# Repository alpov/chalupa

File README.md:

# chalupa
Cottage GSM Weather Station

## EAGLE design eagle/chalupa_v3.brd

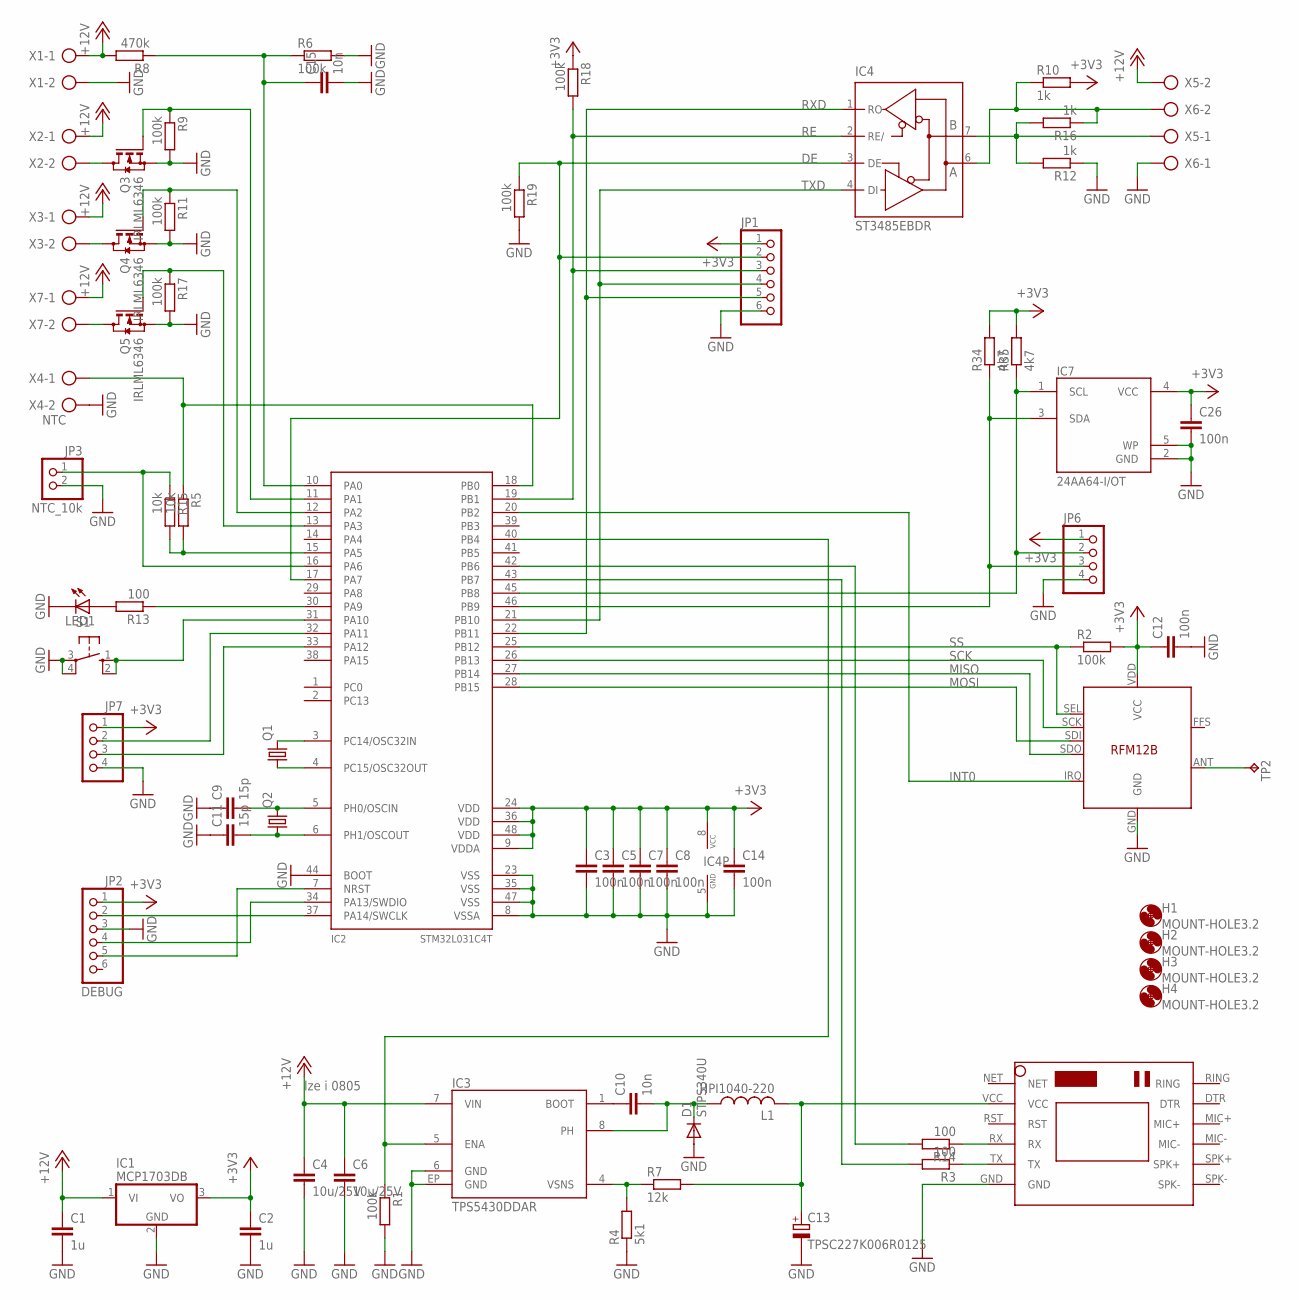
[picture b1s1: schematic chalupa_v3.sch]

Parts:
C1, C2: 1u; C0603
C3, C5, C7, C8, C12, C14, C26: 100n; C0603
C4, C6: 10u/25V; C1206
C9, C11: 15p; C0603
C10, C15: 10n; C0603
C13: TPSC227K006R0125; SMC_C
D1: STPS340U; SMB
H1, H2, H3, H4: MOUNT-HOLE3.2; 3,2
IC1: MCP1703DB; SOT223
IC2: STM32L031C4T; LQFP48
IC3: TPS5430DDAR; DDA
IC4: ST3485EBDR; SO08
IC5: SIM800LMODULE
IC7: 24AA64-I/OT; SOT23-5
JP1: PINHD-1X6; 1X06
JP2: DEBUG; 1X06
JP3: NTC_10k; 1X02
JP6, JP7: PINHD-1X4; 1X04
L1: HPI1040-220; HPI1040
LED1: LEDCHIP-LED0805; CHIP-LED0805
Q1: CRYSTALTC38H; TC38H
Q2: CRYSTALHC49UP; HC49UP
Q3, Q4, Q5: IRLML6346; SOT23
R1, R2, R6, R9, R11, R17, R18, R19: 100k; R0603
R3, R13, R14: 100; R0603
R4: 5k1; R0603
R5, R15: 10k; R0603
R7: 12k; R0603
R8: 470k; R0603
R10, R12, R16: 1k; R0603
R34, R35: 4k7; R0603
RFM12B: RFM12B
S1: 10-XX; B3F-10XX
TP2: ANT868; B2,54
X1, X2, X3, X5, X6, X7: AK500/2
X4: NTC; AK500/2

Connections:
+3V3: C2.1, C3.1, C5.1, C7.1, C8.1, C12.1, C14.1, C26.1, IC1.3 (VO), IC2.9 (VDDA), IC2.24 (VDD), IC2.36 (VDD), IC2.48 (VDD), IC4.8 (VCC), IC7.4 (VCC), JP1.1, JP2.1, JP6.1, JP7.1, R2.2, R10.2, R18.1, R34.2, R35.2, RFM12B.VDD (VCC)
+12V: C1.1, C4.1, C6.1, IC1.1 (VI), IC3.7 (VIN), R8.2, X1.1, X2.1, X3.1, X5.2, X7.1
DE: IC2.17 (PA7), IC4.3 (DE), JP1.2, R19.1
EEP_SCL: IC2.45 (PB8), IC7.1 (SCL), JP6.2, R35.1
EEP_SDA: IC2.46 (PB9), IC7.3 (SDA), JP6.3, R34.1
GND: C1.2, C2.2, C3.2, C4.2, C5.2, C6.2, C7.2, C8.2, C9.1, C11.1, C12.2, C13.-, C14.2, C15.2, C26.2, D1.A, IC1.2 (GND), IC2.8 (VSSA), IC2.23 (VSS), IC2.35 (VSS), IC2.44 (BOOT), IC2.47 (VSS), IC3.6 (GND), IC3.EP (GND), IC4.5 (GND), IC5.GND, IC7.2 (GND), IC7.5 (WP), JP1.6, JP2.3, JP3.2, JP6.4, JP7.4, LED1.C, Q3.2 (S), Q4.2 (S), Q5.2 (S), R1.2, R4.1, R6.2, R9.2, R11.2, R12.1, R17.2, R19.2, RFM12B.GND, S1.3, S1.4 (P1), X1.2, X4.2, X6.1
GSM_EN: IC2.40 (PB4), IC3.5 (ENA), R1.1
INT0: IC2.20 (PB2), RFM12B.IRQ
MISO: IC2.27 (PB14), RFM12B.SDO
MOSI: IC2.28 (PB15), RFM12B.SDI
unnamed: C11.2, IC2.6 (PH1/OSCOUT), Q2.1
unnamed: IC5.TX, R3.1
unnamed: C9.2, IC2.5 (PH0/OSCIN), Q2.2
unnamed: IC2.4 (PC15/OSC32OUT), Q1.1
unnamed: IC2.3 (PC14/OSC32IN), Q1.2
unnamed: RFM12B.ANT, TP2.PP
unnamed: IC2.42 (PB6), R14.2
unnamed: C10.1, IC3.1 (BOOT)
unnamed: C13.+, IC5.VCC, L1.2, R7.2
unnamed: C10.2, D1.C, IC3.8 (PH), L1.1
unnamed: Q5.3 (D), X7.2
unnamed: IC5.RX, R14.1
unnamed: LED1.A, R13.2
unnamed: IC2.31 (PA10), S1.1 (S), S1.2 (S1)
unnamed: IC2.18 (PB0), R5.1, X4.1
unnamed: Q3.3 (D), X2.2
unnamed: Q4.3 (D), X3.2
unnamed: IC2.13 (PA3), Q5.1 (G), R17.1
unnamed: C15.1, IC2.10 (PA0), R6.1, R8.1
unnamed: IC4.7 (B), R12.2, R16.2, X5.1
unnamed: IC2.11 (PA1), Q3.1 (G), R9.1
unnamed: IC3.4 (VSNS), R4.2, R7.1
unnamed: IC2.12 (PA2), Q4.1 (G), R11.1
unnamed: IC2.15 (PA5), R5.2, R15.2
unnamed: IC2.16 (PA6), JP3.1, R15.1
unnamed: IC2.30 (PA9), R13.1
unnamed: IC2.32 (PA11), JP7.2
unnamed: IC2.33 (PA12), JP7.3
unnamed: IC4.6 (A), R10.1, R16.1, X6.2
unnamed: IC2.34 (PA13/SWDIO), JP2.4
unnamed: IC2.37 (PA14/SWCLK), JP2.2
unnamed: IC2.7 (NRST), JP2.5
RE: IC2.19 (PB1), IC4.2 (RE/), JP1.3, R18.2
RXD: IC2.22 (PB11), IC4.1 (RO), JP1.5
SCK: IC2.26 (PB13), RFM12B.SCK
SS: IC2.25 (PB12), R2.1, RFM12B.SEL
TX1: IC2.43 (PB7), R3.2
TXD: IC2.21 (PB10), IC4.4 (DI), JP1.4

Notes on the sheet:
lze i 0805

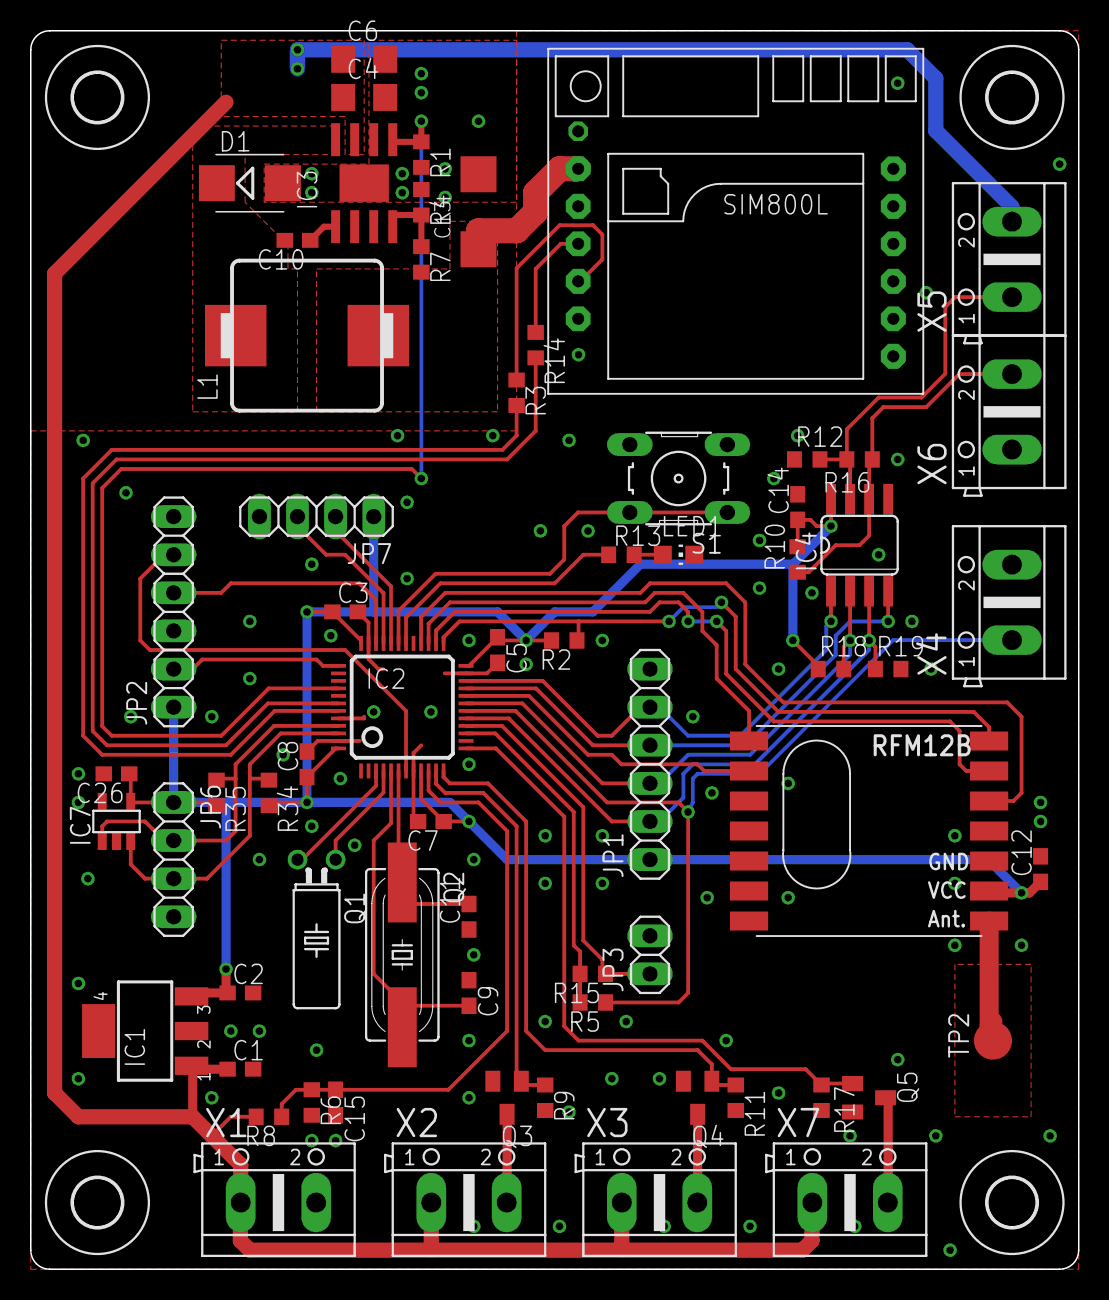
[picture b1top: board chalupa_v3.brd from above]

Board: 2 copper layers, 69.8 x 82.5 mm, 70 parts (0 on the bottom side), 48 nets.

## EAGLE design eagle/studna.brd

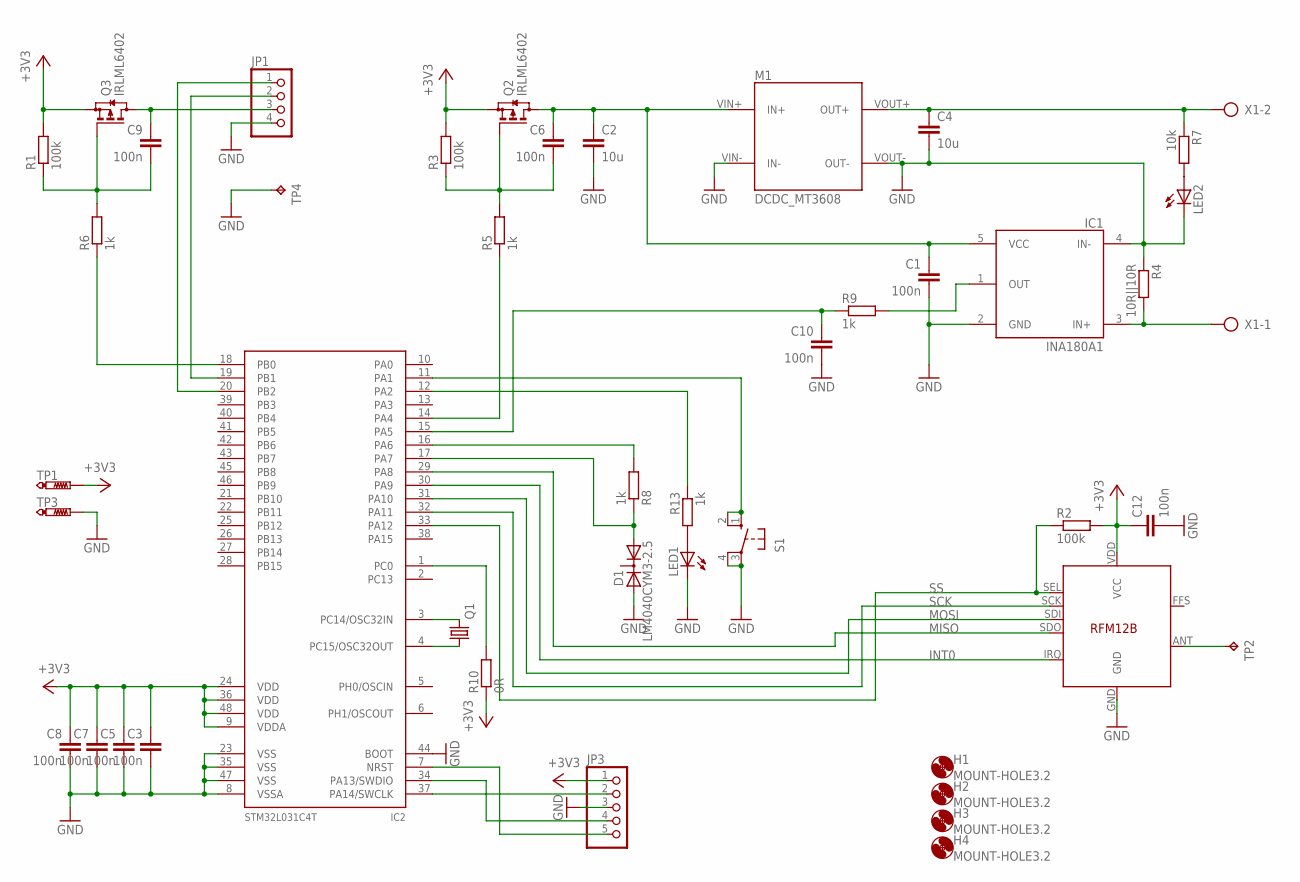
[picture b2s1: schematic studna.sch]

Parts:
C1, C3, C5, C6, C7, C8, C9, C10, C12: 100n; C0603
C2, C4: 10u; C1206K
D1: LM4040CYM3-2.5; SOT23
H1, H2, H3, H4: MOUNT-HOLE3.2; 3,2
IC1: INA180A1; SOT23-5L
IC2: STM32L031C4T; LQFP48
IC3: RFM12B
JP1: PINHD-1X4; 1X04
JP3: PINHD-1X5; 1X05
LED1, LED2: LED3MM
M1: DCDC_MT3608
Q1: CRYSTALTC38H; TC38H
Q2, Q3: IRLML6402; SOT23
R1, R2, R3: 100k; R0603
R4: 10R||10R; R1206
R5, R6, R8, R9, R13: 1k; R0603
R7: 10k; R0603
R10: 0R; R0603
S1: 10-XX; B3F-10XX
TP1, TP3: PTR1PAD1-17Y; P1-17Y
TP2: TPB2,54; B2,54
TP4: TPPAD1-13Y; P1-13Y
X1: AK500/2

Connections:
+3V3: C3.1, C5.1, C7.1, C8.1, C12.1, IC2.9 (VDDA), IC2.24 (VDD), IC2.36 (VDD), IC2.48 (VDD), IC3.VDD (VCC), JP3.1, Q2.2 (S), Q3.2 (S), R1.2, R2.2, R3.2, R10.1, TP1.TP
DCDC_3V3: C1.1, C2.1, C6.1, IC1.5 (VCC), M1.VIN+ (IN+), Q2.3 (D)
DISP_3V3: C9.1, JP1.3, Q3.3 (D)
GND: C1.2, C2.2, C3.2, C4.2, C5.2, C7.2, C8.2, C10.2, C12.2, D1.2 (A2), IC1.2 (GND), IC1.4 (IN-), IC2.8 (VSSA), IC2.23 (VSS), IC2.35 (VSS), IC2.44 (BOOT), IC2.47 (VSS), IC3.GND, JP1.4, JP3.3, LED1.K (C), LED2.K (C), M1.VIN- (IN-), M1.VOUT- (OUT-), R4.1, S1.3, S1.4 (P1), TP3.TP, TP4.TP
INT0: IC2.30 (PA9), IC3.IRQ
MISO: IC2.29 (PA8), IC3.SDO
MOSI: IC2.31 (PA10), IC3.SDI
unnamed: C6.2, Q2.1 (G), R3.1, R5.2
unnamed: D1.1 (A1), IC2.17 (PA7), R8.1
unnamed: IC1.3 (IN+), R4.2, X1.1
unnamed: IC2.4 (PC15/OSC32OUT), Q1.1
unnamed: IC2.3 (PC14/OSC32IN), Q1.2
unnamed: IC3.ANT, TP2.TP
unnamed: C4.1, M1.VOUT+ (OUT+), R7.1, X1.2
unnamed: C10.1, IC2.15 (PA5), R9.1
unnamed: LED2.A, R7.2
unnamed: IC2.19 (PB1), JP1.2
unnamed: IC2.14 (PA4), R5.1
unnamed: IC1.1 (OUT), R9.2
unnamed: IC2.16 (PA6), R8.2
unnamed: LED1.A, R13.2
unnamed: IC2.11 (PA1), S1.1 (S), S1.2 (S1)
unnamed: IC2.1 (PC0), R10.2
unnamed: C9.2, Q3.1 (G), R1.1, R6.2
unnamed: IC2.18 (PB0), R6.1
unnamed: IC2.20 (PB2), JP1.1
unnamed: IC2.12 (PA2), R13.1
unnamed: IC2.34 (PA13/SWDIO), JP3.4
unnamed: IC2.37 (PA14/SWCLK), JP3.2
unnamed: IC2.7 (NRST), JP3.5
SCK: IC2.32 (PA11), IC3.SCK
SS: IC2.33 (PA12), IC3.SEL, R2.1

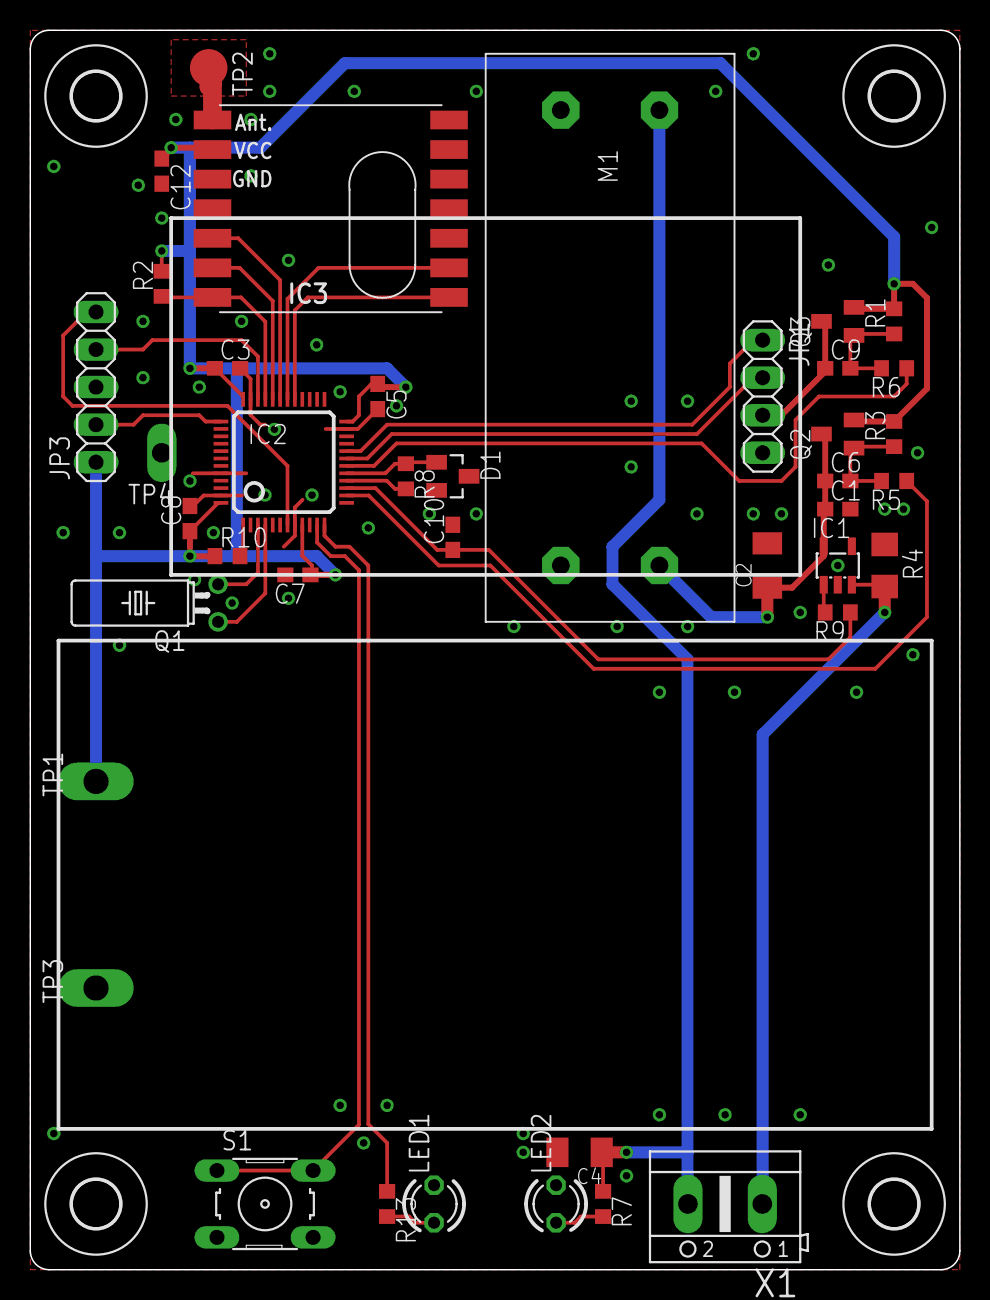
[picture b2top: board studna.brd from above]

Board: 2 copper layers, 62.9 x 83.8 mm, 44 parts (0 on the bottom side), 32 nets.

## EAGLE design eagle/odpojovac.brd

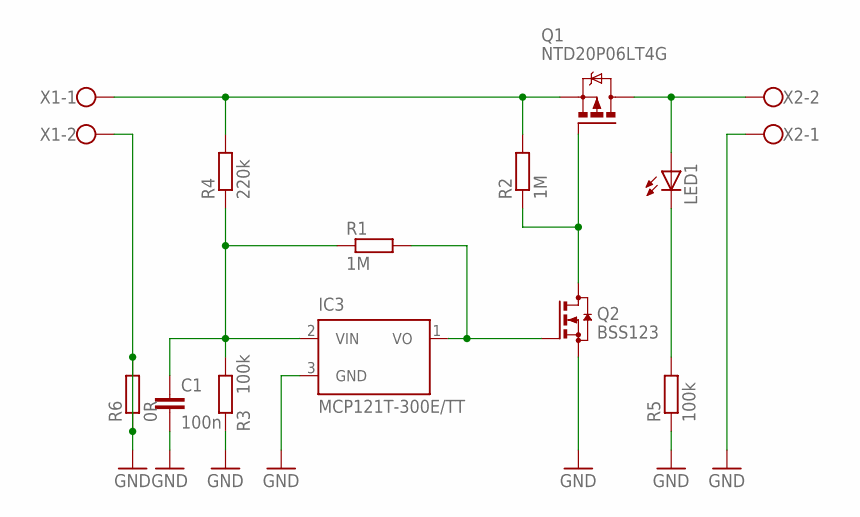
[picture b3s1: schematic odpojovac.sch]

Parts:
C1: 100n; C0805K
IC3: MCP121T-300E/TT; SOT23
LED1: LEDCHIPLED_0805; CHIPLED_0805
Q1: NTD20P06LT4G; D-PAK_TO252AA
Q2: BSS123; SOT23
R1, R2: 1M; R0805
R3, R5: 100k; R0805
R4: 220k; R0805
R6: 0R; R1206
X1, X2: W237-102

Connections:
GND: C1.2, IC3.3 (GND), Q2.2 (S), R3.1, R5.1, R6.1, R6.2, X1.2, X2.1
unnamed: LED1.A, Q1.4 (D), X2.2
unnamed: LED1.C, R5.2
unnamed: Q1.3 (S), R2.2, R4.2, X1.1
unnamed: IC3.1 (VO), Q2.1 (G), R1.2
unnamed: C1.1, IC3.2 (VIN), R1.1, R3.2, R4.1
unnamed: Q1.1 (G), Q2.3 (D), R2.1

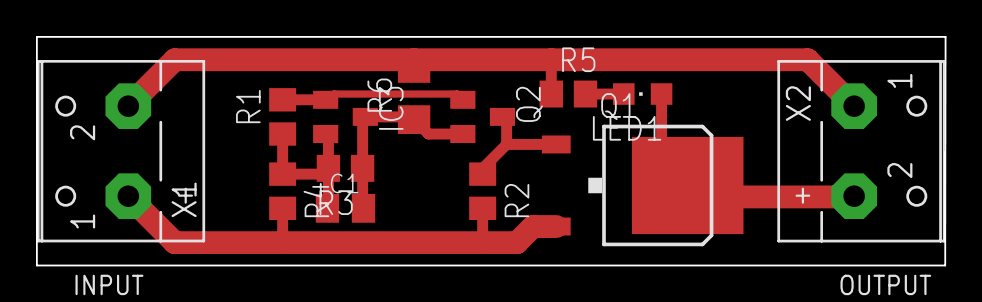
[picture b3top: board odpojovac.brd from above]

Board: 2 copper layers, 50.5 x 12.7 mm, 13 parts (0 on the bottom side), 7 nets.

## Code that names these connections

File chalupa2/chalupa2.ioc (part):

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Mcu.Name=STM32L051C(6-8)Tx
Mcu.Package=LQFP48
Mcu.UserName=STM32L051C8Tx
PA0.Mode=IN0
PA0.Signal=ADC_IN0
PA1.GPIOParameters=GPIO_Label
PA1.GPIO_Label=OUT1
PA1.Signal=GPIO_Output
PA10.GPIOParameters=GPIO_PuPd,GPIO_Label
PA10.GPIO_Label=BTN1
PA10.GPIO_PuPd=GPIO_PULLUP
PA10.Signal=GPIO_Input
PA13.Mode=Serial_Wire
PA13.Signal=SYS_SWDIO
PA14.Mode=Serial_Wire
PA14.Signal=SYS_SWCLK
PA2.GPIOParameters=GPIO_Label
PA2.GPIO_Label=OUT2
PA2.Signal=GPIO_Output
PA3.GPIOParameters=GPIO_Label
PA3.GPIO_Label=OUT3
PA3.Signal=GPIO_Output
PA5.GPIOParameters=GPIO_Label
PA5.GPIO_Label=NTC_EN
PA5.Signal=GPIO_Output
PA6.Mode=IN6
PA6.Signal=ADC_IN6
PA7.GPIOParameters=GPIO_Label
PA7.GPIO_Label=LPUART1_DE
PA7.Signal=GPIO_Output
PA9.GPIOParameters=GPIO_Label
PA9.GPIO_Label=LED1
PA9.Signal=GPIO_Output
PB0.Mode=IN8
PB0.Signal=ADC_IN8
PB1.GPIOParameters=PinState,GPIO_Label
PB1.GPIO_Label=LPUART1_RE
PB1.PinState=GPIO_PIN_SET
PB1.Signal=GPIO_Output
PB10.GPIOParameters=GPIO_Label
PB10.GPIO_Label=LPUART1_TX
PB10.Signal=GPIO_Output
PB11.GPIOParameters=GPIO_PuPd,GPIO_Label
PB11.GPIO_Label=LPUART1_RX
PB11.GPIO_PuPd=GPIO_PULLUP
PB11.Signal=GPIO_Input
PB12.GPIOParameters=GPIO_Speed,PinState,GPIO_Label
PB12.GPIO_Label=SPI2_NSS
PB12.GPIO_Speed=GPIO_SPEED_FREQ_VERY_HIGH
PB12.PinState=GPIO_PIN_SET
PB12.Signal=GPIO_Output
PB13.GPIOParameters=GPIO_PuPd
PB13.GPIO_PuPd=GPIO_PULLDOWN
PB13.Mode=Full_Duplex_Master
PB13.Signal=SPI2_SCK
PB14.GPIOParameters=GPIO_PuPd
PB14.GPIO_PuPd=GPIO_PULLDOWN
PB14.Mode=Full_Duplex_Master
PB14.Signal=SPI2_MISO
PB15.GPIOParameters=GPIO_PuPd
PB15.GPIO_PuPd=GPIO_PULLDOWN
PB15.Mode=Full_Duplex_Master
PB15.Signal=SPI2_MOSI
PB2.GPIOParameters=GPIO_PuPd,GPIO_Label,GPIO_ModeDefaultEXTI
PB2.GPIO_Label=RFM_INT0
PB2.GPIO_ModeDefaultEXTI=GPIO_MODE_IT_FALLING
PB2.GPIO_PuPd=GPIO_PULLUP
PB2.Signal=GPXTI2
PB4.GPIOParameters=GPIO_Label
PB4.GPIO_Label=GSM_EN
PB4.Signal=GPIO_Output
PB6.Mode=Asynchronous
PB6.Signal=USART1_TX
PB7.GPIOParameters=GPIO_PuPd
PB7.GPIO_PuPd=GPIO_PULLDOWN
PB7.Mode=Asynchronous
PB7.Signal=USART1_RX
PB8.GPIOParameters=GPIO_Label
PB8.GPIO_Label=I2C1_SCL
PB8.Signal=GPIO_Input
PB9.GPIOParameters=GPIO_Label
PB9.GPIO_Label=I2C1_SDA
PB9.Signal=GPIO_Input
PH0-OSC_IN.Mode=HSE-External-Oscillator
PH0-OSC_IN.Signal=RCC_OSC_IN
PH1-OSC_OUT.Mode=HSE-External-Oscillator
PH1-OSC_OUT.Signal=RCC_OSC_OUT
RCC.HSE_VALUE=8000000
RCC.SYSCLKFreq_VALUE=8000000
RCC.SYSCLKSource=RCC_SYSCLKSOURCE_HSE
board=custom

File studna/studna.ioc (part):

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Mcu.Name=STM32L051C(6-8)Tx
Mcu.Package=LQFP48
Mcu.UserName=STM32L051C8Tx
PA1.GPIOParameters=GPIO_PuPd,GPIO_Label
PA1.GPIO_Label=BTN1
PA1.GPIO_PuPd=GPIO_PULLUP
PA1.Signal=GPIO_Input
PA10.GPIOParameters=GPIO_Speed,GPIO_Label
PA10.GPIO_Label=RFM_MOSI
PA10.GPIO_Speed=GPIO_SPEED_FREQ_HIGH
PA10.Signal=GPIO_Output
PA11.GPIOParameters=GPIO_Speed,GPIO_Label
PA11.GPIO_Label=RFM_SCK
PA11.GPIO_Speed=GPIO_SPEED_FREQ_HIGH
PA11.Signal=GPIO_Output
PA12.GPIOParameters=GPIO_Speed,PinState,GPIO_Label
PA12.GPIO_Label=RFM_SS
PA12.GPIO_Speed=GPIO_SPEED_FREQ_HIGH
PA12.PinState=GPIO_PIN_SET
PA12.Signal=GPIO_Output
PA13.Mode=Serial_Wire
PA13.Signal=SYS_SWDIO
PA14.Mode=Serial_Wire
PA14.Signal=SYS_SWCLK
PA2.GPIOParameters=GPIO_Label
PA2.GPIO_Label=LED1
PA2.Signal=GPIO_Output
PA4.GPIOParameters=PinState,GPIO_Label
PA4.GPIO_Label=DCDC_SHDN
PA4.PinState=GPIO_PIN_SET
PA4.Signal=GPIO_Output
PA5.GPIOParameters=GPIO_Label
PA5.GPIO_Label=ADC_INA
PA5.Mode=IN5
PA5.Signal=ADC_IN5
PA6.GPIOParameters=GPIO_Label
PA6.GPIO_Label=REF_EN
PA6.Signal=GPIO_Output
PA7.GPIOParameters=GPIO_Label
PA7.GPIO_Label=ADC_REF
PA7.Mode=IN7
PA7.Signal=ADC_IN7
PA8.GPIOParameters=GPIO_Label
PA8.GPIO_Label=RFM_MISO
PA8.Signal=GPIO_Input
PA9.GPIOParameters=GPIO_PuPd,GPIO_Label,GPIO_ModeDefaultEXTI
PA9.GPIO_Label=RFM_INT0
PA9.GPIO_ModeDefaultEXTI=GPIO_MODE_IT_FALLING
PA9.GPIO_PuPd=GPIO_PULLUP
PA9.Signal=GPXTI9
PB0.GPIOParameters=PinState,GPIO_Label
PB0.GPIO_Label=DISP_SHDN
PB0.PinState=GPIO_PIN_SET
PB0.Signal=GPIO_Output
PB1.GPIOParameters=GPIO_Label
PB1.GPIO_Label=DISP_DIO
PB1.Signal=GPIO_Output
PB2.GPIOParameters=GPIO_Label
PB2.GPIO_Label=DISP_CLK
PB2.Signal=GPIO_Output
PC14-OSC32_IN.Mode=LSE-External-Oscillator
PC14-OSC32_IN.Signal=RCC_OSC32_IN
PC15-OSC32_OUT.Mode=LSE-External-Oscillator
PC15-OSC32_OUT.Signal=RCC_OSC32_OUT
RCC.HSE_VALUE=8000000
RCC.SYSCLKFreq_VALUE=16000000
RCC.SYSCLKSource=RCC_SYSCLKSOURCE_HSI
board=custom

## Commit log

2022-12-09 SVN revision 1442
2024-02-08 Eagle: odpojovac baterie
2024-07-10 Second generation of RX, added well monitor
